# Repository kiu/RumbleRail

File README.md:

RumbleRail
==========

a standalone and modular floppy music player

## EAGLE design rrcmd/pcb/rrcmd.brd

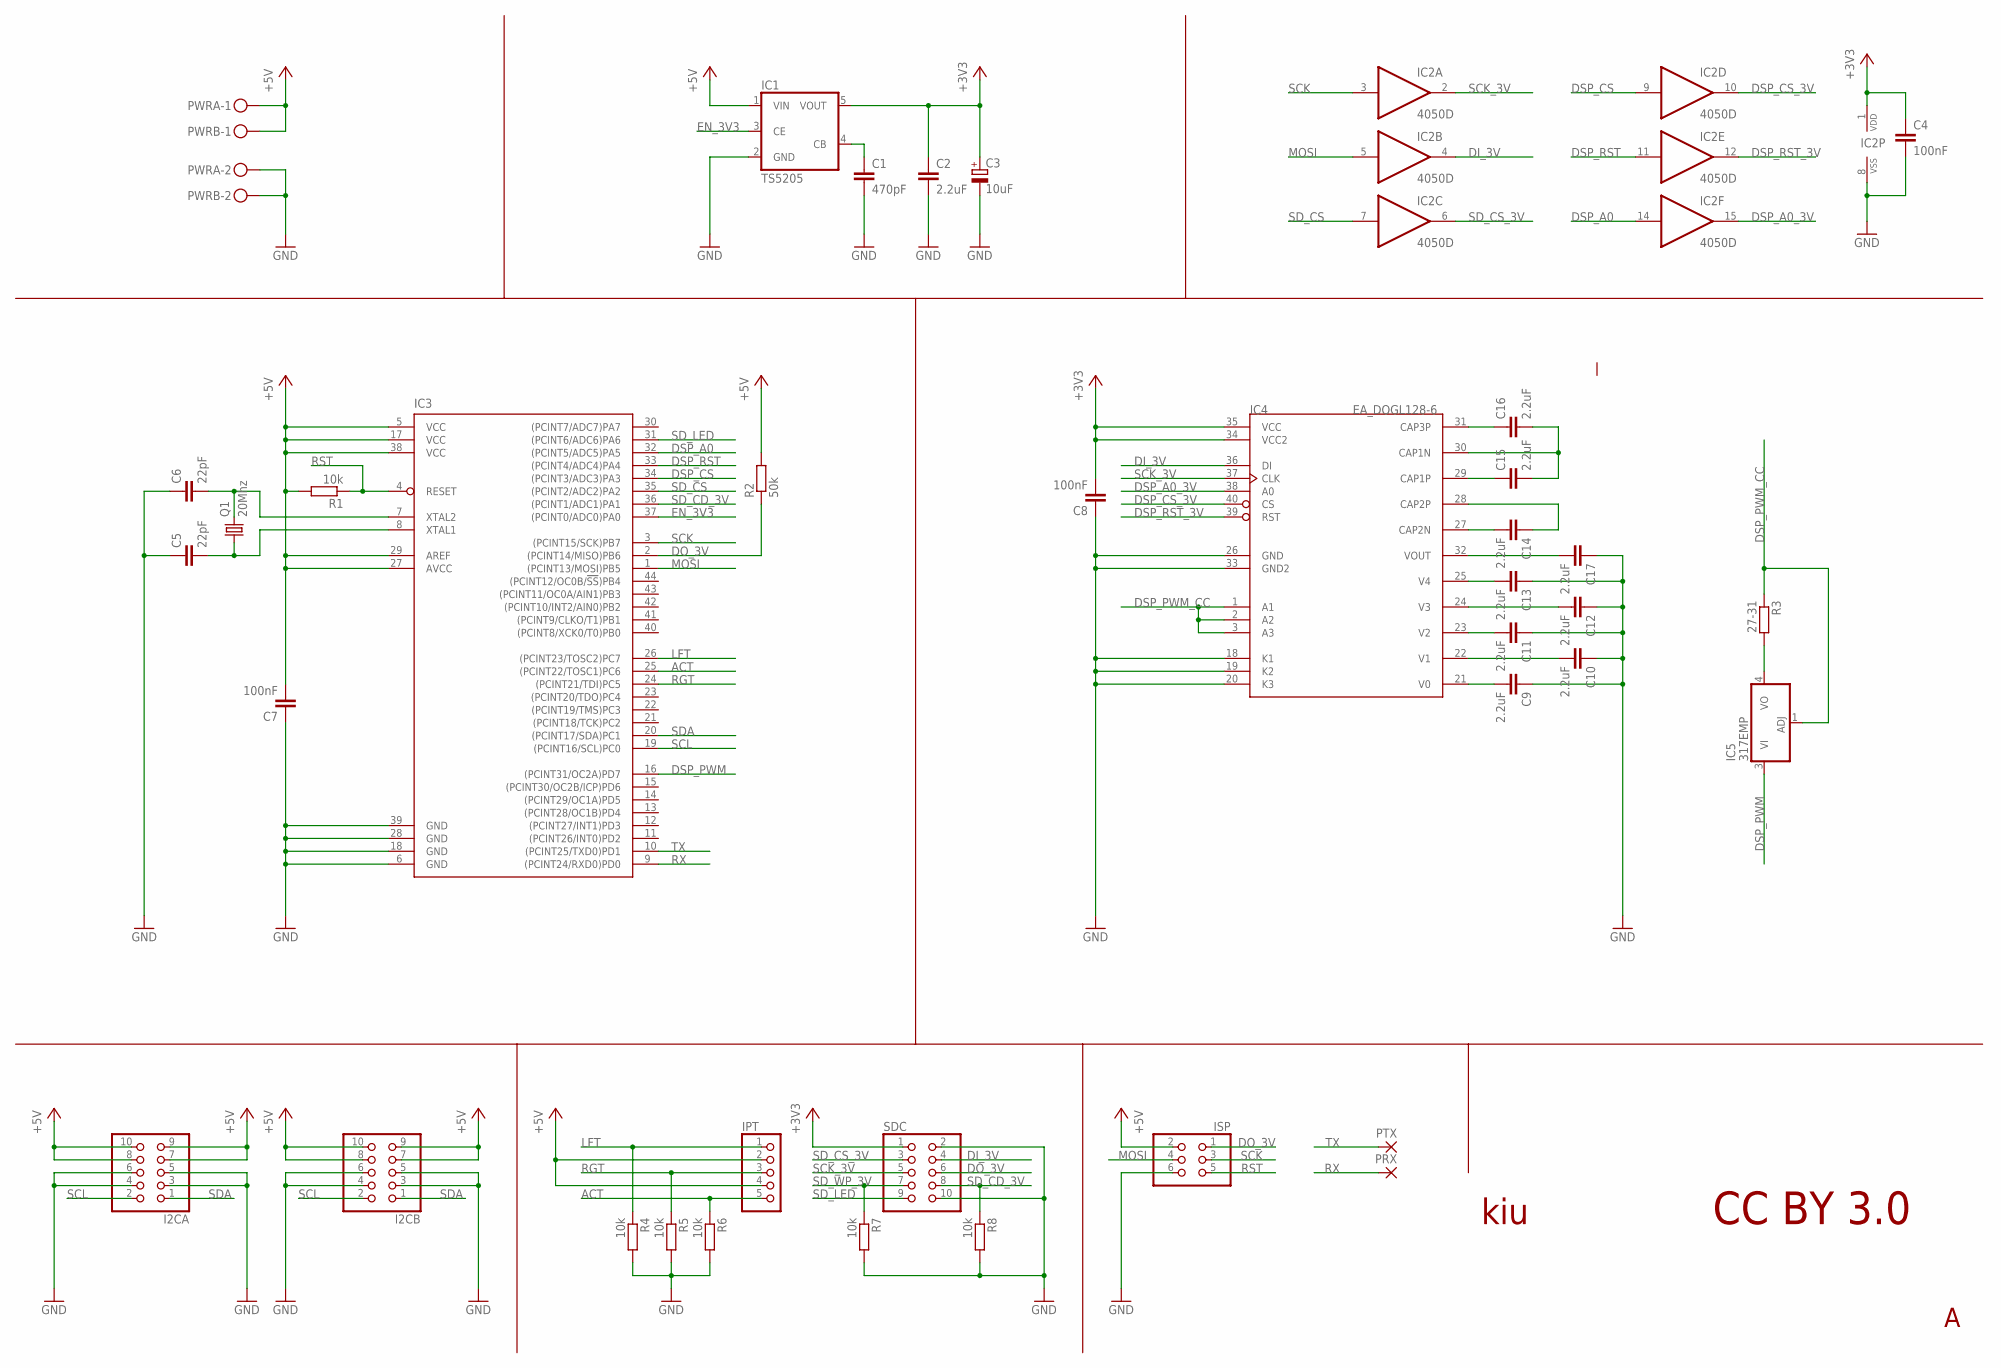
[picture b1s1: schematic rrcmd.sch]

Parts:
C1: 470pF; C0805
C2, C9, C10, C11, C12, C13, C14, C15, C16, C17: 2.2uF; C0805
C3: 10uF; CT3216
C4, C7, C8: 100nF; C0805
C5, C6: 22pF; C0805
I2CA, I2CB: PINHD-2X5; 2X05
IC1: TS5205; SOT25
IC2: 4050D; SO16
IC3: ATMEGA644A; TQFP44
IC4: EA_DOGL128-6
IC5: 317EMP; SOT223
IPT: PINHD-1X5; 1X05
ISP: PINHD-2X3; 2X03
PRX: SMD2; SMD1,27-2,54
PTX: SMD2; SMD1,27-2,54
PWRA: MKDSN1,5/2-5,08
PWRB: MKDSN1,5/2-5,08
Q1: 20Mhz; HC49UP
R1, R4, R5, R6, R7, R8: 10k; R0805
R2: 50k; R0805
R3: 27-31; R0805
SDC: PINHD-2X5; 2X05

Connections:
+3V3: C2.1, C3.+, C4.1, C8.2, IC1.5 (VOUT), IC2.1 (VDD), IC4.34 (VCC2), IC4.35 (VCC), SDC.1
+5V: C7.2, I2CA.7, I2CA.8, I2CA.9, I2CA.10, I2CB.7, I2CB.8, I2CB.9, I2CB.10, IC1.1 (VIN), IC3.5 (VCC), IC3.17 (VCC), IC3.27 (AVCC), IC3.29 (AREF), IC3.38 (VCC), IPT.2, IPT.4, ISP.2, PWRA.1, PWRB.1, R1.2, R2.2
ACT: IC3.25 ((PCINT22/TOSC1)PC6), IPT.5, R6.1
CAP1N: C15.2, C16.2, IC4.30 (CAP1N)
CAP1P: C15.1, IC4.29 (CAP1P)
CAP2N: C14.2, IC4.27 (CAP2N)
CAP2P: C14.1, IC4.28 (CAP2P)
CAP3P: C16.1, IC4.31 (CAP3P)
DI_3V: IC2.4 (O), IC4.36 (DI), SDC.4
DO_3V: IC3.2 ((PCINT14/MISO)PB6), ISP.1, R2.1, SDC.6
DSP_A0: IC2.14 (I), IC3.32 ((PCINT5/ADC5)PA5)
DSP_A0_3V: IC2.15 (O), IC4.38 (A0)
DSP_CS: IC2.9 (I), IC3.34 ((PCINT3/ADC3)PA3)
DSP_CS_3V: IC2.10 (O), IC4.40 (CS)
DSP_PWM: IC3.16 ((PCINT31/OC2A)PD7), IC5.3 (VI)
DSP_PWM_CC: IC4.1 (A1), IC4.2 (A2), IC4.3 (A3), IC5.1 (ADJ), R3.1
DSP_RST: IC2.11 (I), IC3.33 ((PCINT4/ADC4)PA4)
DSP_RST_3V: IC2.12 (O), IC4.39 (RST)
EN_3V3: IC1.3 (CE), IC3.37 ((PCINT0/ADC0)PA0)
GND: C1.2, C2.2, C3.-, C4.2, C5.1, C6.1, C7.1, C8.1, C9.1, C10.1, C11.1, C12.1, C13.1, C17.1, I2CA.3, I2CA.4, I2CA.5, I2CA.6, I2CB.3, I2CB.4, I2CB.5, I2CB.6, IC1.2 (GND), IC2.8 (VSS), IC3.6 (GND), IC3.18 (GND), IC3.28 (GND), IC3.39 (GND), IC4.18 (K1), IC4.19 (K2), IC4.20 (K3), IC4.26 (GND), IC4.33 (GND2), ISP.6, PWRA.2, PWRB.2, R4.2, R5.2, R6.2, R7.2, R8.2, SDC.2, SDC.10
LFT: IC3.26 ((PCINT23/TOSC2)PC7), IPT.1, R4.1
MOSI: IC2.5 (I), IC3.1 ((PCINT13/MOSI)PB5), ISP.4
unnamed: C1.1, IC1.4 (CB)
unnamed: C12.2, IC4.24 (V3)
unnamed: C13.2, IC4.25 (V4)
unnamed: C11.2, IC4.23 (V2)
unnamed: C10.2, IC4.22 (V1)
unnamed: C9.2, IC4.21 (V0)
unnamed: C17.2, IC4.32 (VOUT)
unnamed: IC5.4 (VO), R3.2
unnamed: C6.2, IC3.7 (XTAL2), Q1.2
unnamed: C5.2, IC3.8 (XTAL1), Q1.1
RGT: IC3.24 ((PCINT21/TDI)PC5), IPT.3, R5.1
RST: IC3.4 (RESET), ISP.5, R1.1
RX: IC3.9 ((PCINT24/RXD0)PD0), PRX.1
SCK: IC2.3 (I), IC3.3 ((PCINT15/SCK)PB7), ISP.3
SCK_3V: IC2.2 (O), IC4.37 (CLK), SDC.5
SCL: I2CA.2, I2CB.2, IC3.19 ((PCINT16/SCL)PC0)
SDA: I2CA.1, I2CB.1, IC3.20 ((PCINT17/SDA)PC1)
SD_CD_3V: IC3.36 ((PCINT1/ADC1)PA1), R8.1, SDC.8
SD_CS: IC2.7 (I), IC3.35 ((PCINT2/ADC2)PA2)
SD_CS_3V: IC2.6 (O), SDC.3
SD_LED: IC3.31 ((PCINT6/ADC6)PA6), SDC.9
SD_WP_3V: R7.1, SDC.7
TX: IC3.10 ((PCINT25/TXD0)PD1), PTX.1

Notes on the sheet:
CC BY 3.0
kiu

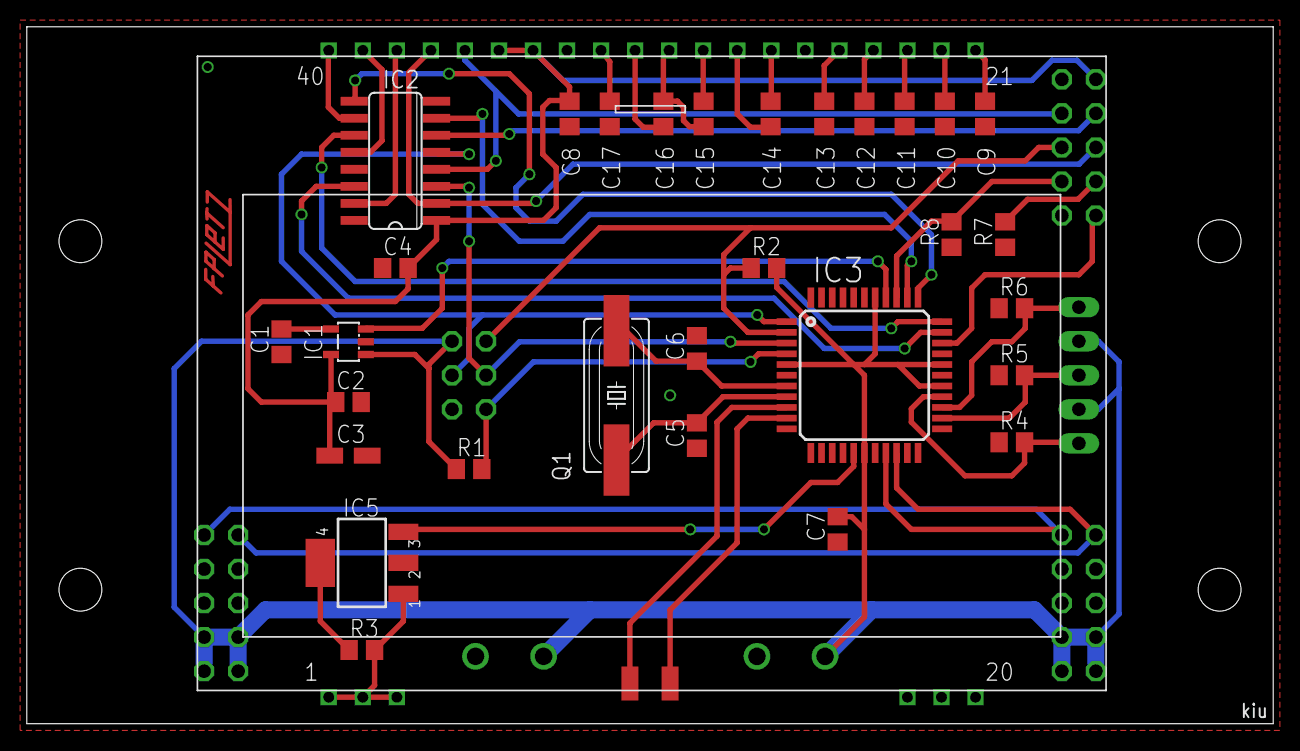
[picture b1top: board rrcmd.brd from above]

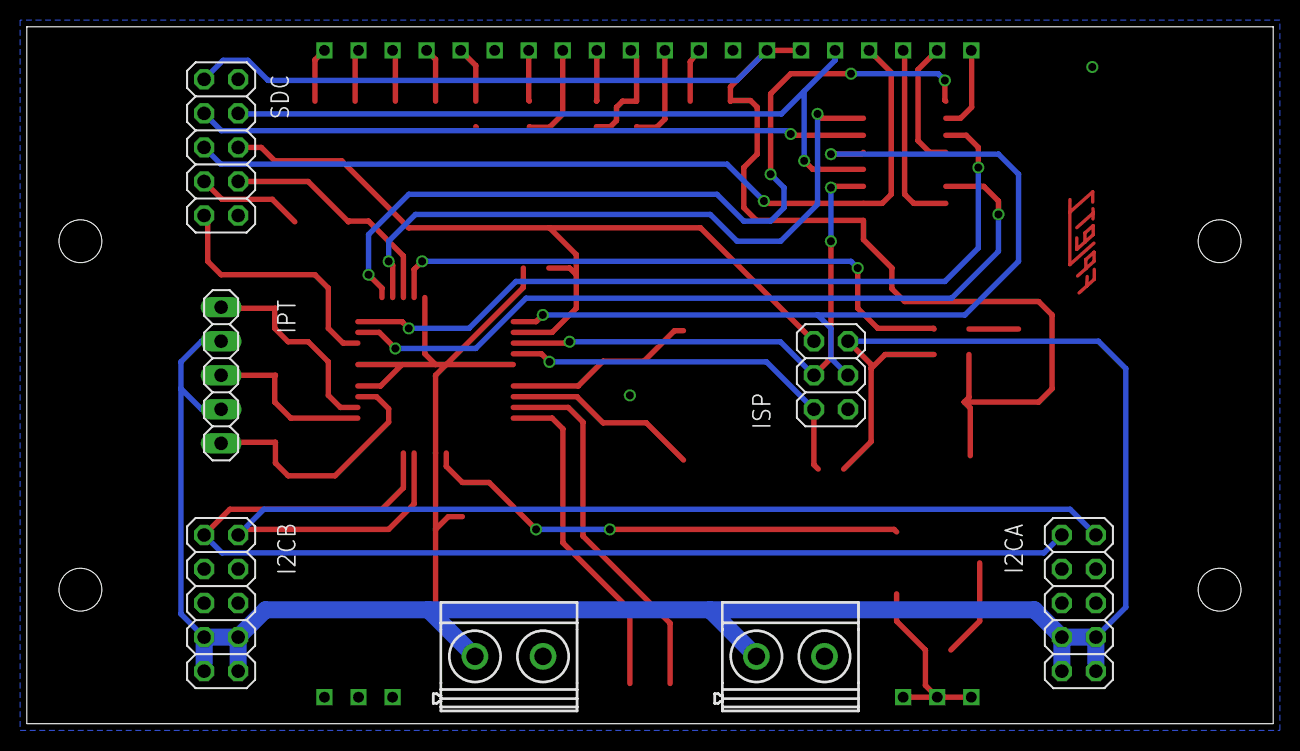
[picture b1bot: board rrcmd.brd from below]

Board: 4 copper layers, 93.0 x 52.0 mm, 40 parts (7 on the bottom side), 45 nets.

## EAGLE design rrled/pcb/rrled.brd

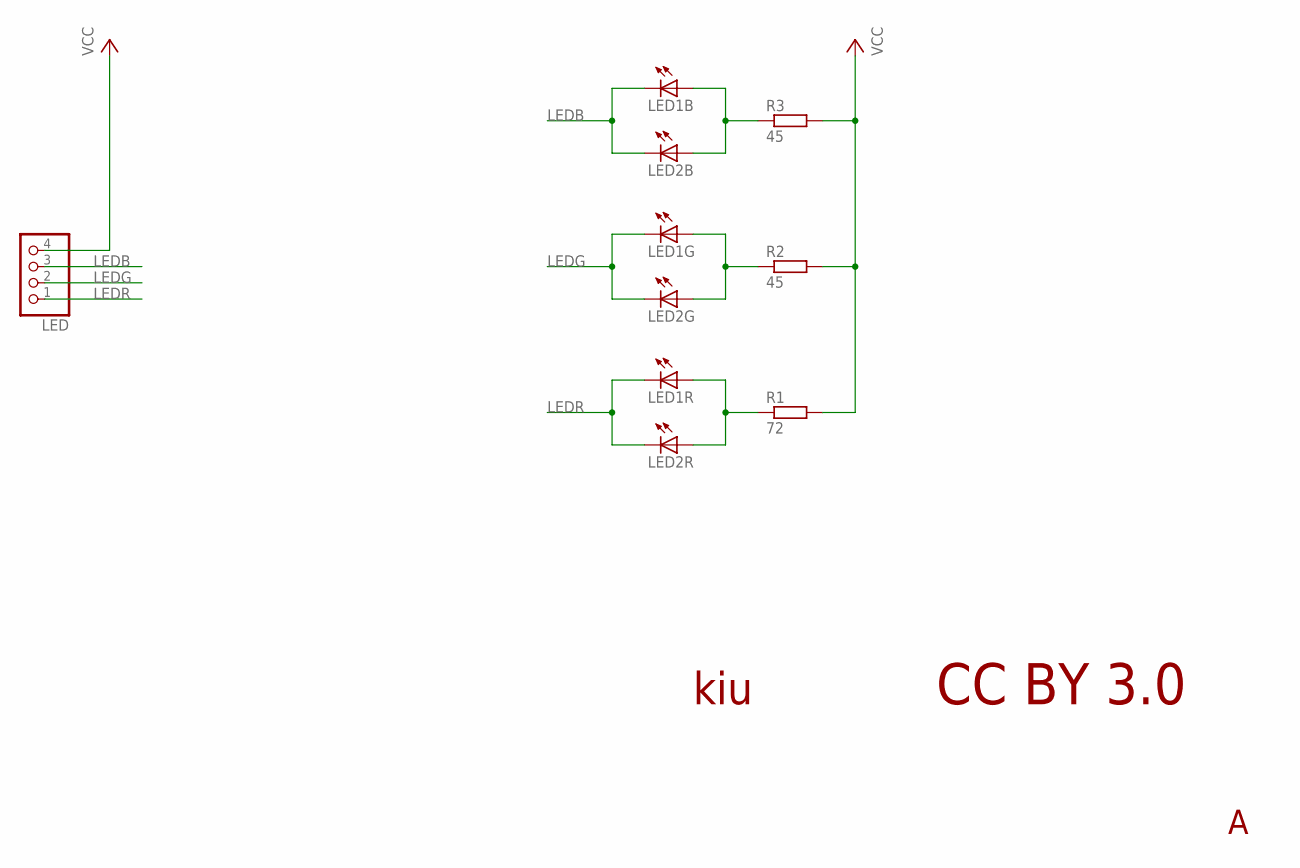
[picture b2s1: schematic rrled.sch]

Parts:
LED: PINHD-1X4; 1X04
LED1, LED2: MULTILED_LRTB_G6TG; P-LCC-6_TOPLED
R1: 72; R0603
R2, R3: 45; R0603

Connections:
LEDB: LED.3, LED1.C3 (C), LED2.C3 (C)
LEDG: LED.2, LED1.C2 (C), LED2.C2 (C)
LEDR: LED.1, LED1.C1 (C), LED2.C1 (C)
unnamed: LED1.A2 (A), LED2.A2 (A), R2.1
unnamed: LED1.A3 (A), LED2.A3 (A), R3.1
unnamed: LED1.A1 (A), LED2.A1 (A), R1.1
VCC: LED.4, R1.2, R2.2, R3.2

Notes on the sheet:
CC BY 3.0
kiu

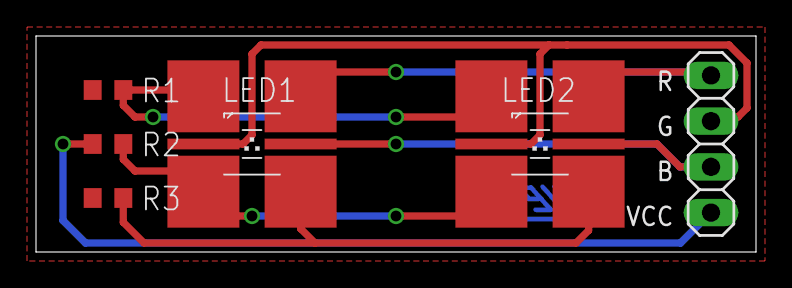
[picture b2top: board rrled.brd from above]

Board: 4 copper layers, 40.0 x 12.0 mm, 6 parts (0 on the bottom side), 7 nets.

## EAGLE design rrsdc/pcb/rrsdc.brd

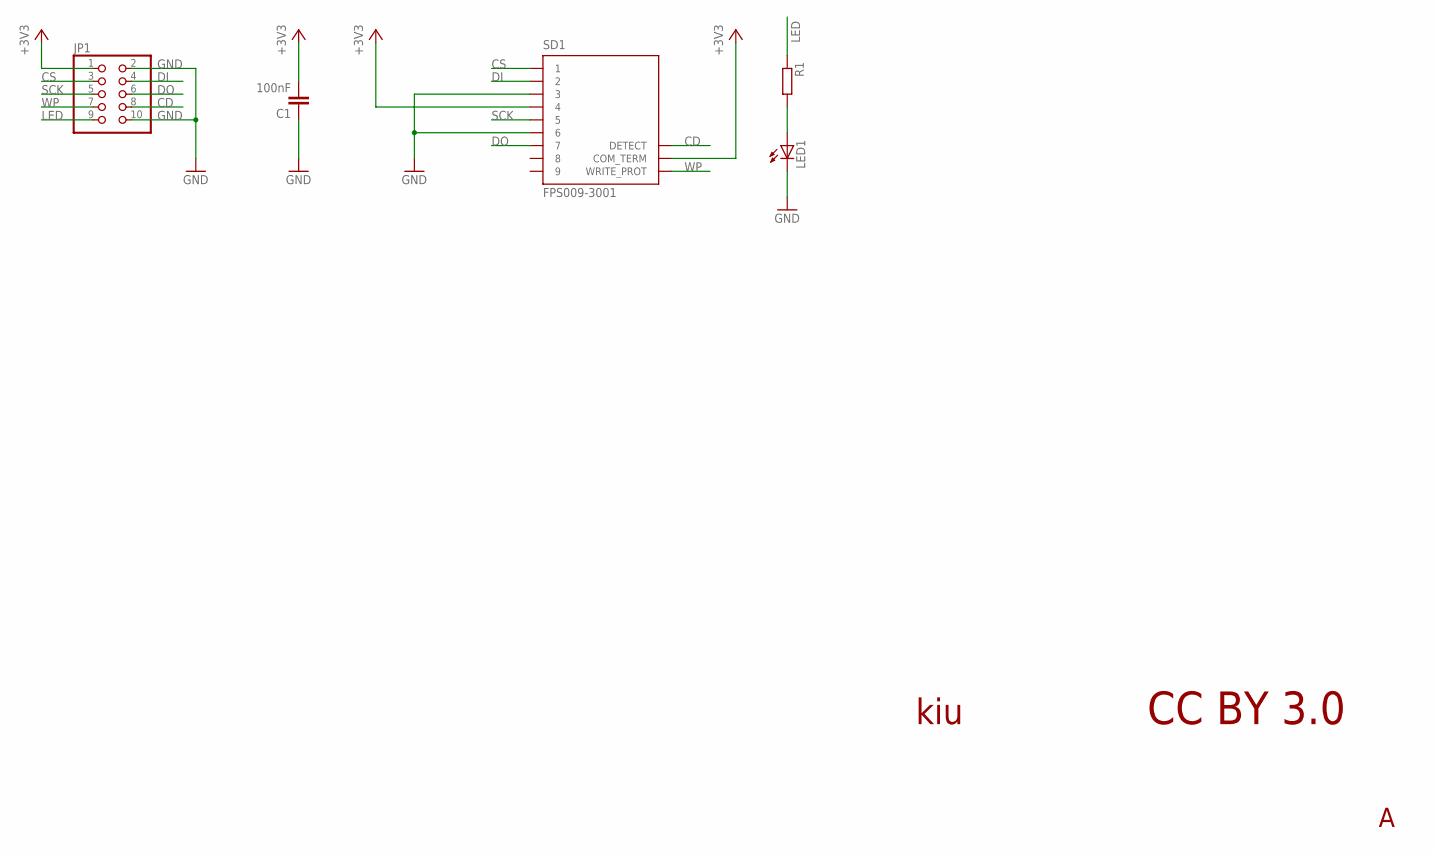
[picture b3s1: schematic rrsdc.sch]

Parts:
C1: 100nF; C0805
JP1: PINHD-2X5; 2X05
LED1: SIDELEDPLCC-NOTHERM; PLCC-2-NOTHERM
R1: R-EU_R0805; R0805
SD1: FPS009-3001; FPS009-3000

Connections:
+3V3: C1.2, JP1.1, SD1.4, SD1.COM_TERM
CD: JP1.8, SD1.DETECT
CS: JP1.3, SD1.1
DI: JP1.4, SD1.2
DO: JP1.6, SD1.7
GND: C1.1, JP1.2, JP1.10, LED1.C, SD1.3, SD1.6
LED: JP1.9, R1.1
unnamed: LED1.A, R1.2
SCK: JP1.5, SD1.5
WP: JP1.7, SD1.WRITE_PROT

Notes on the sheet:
CC BY 3.0
kiu

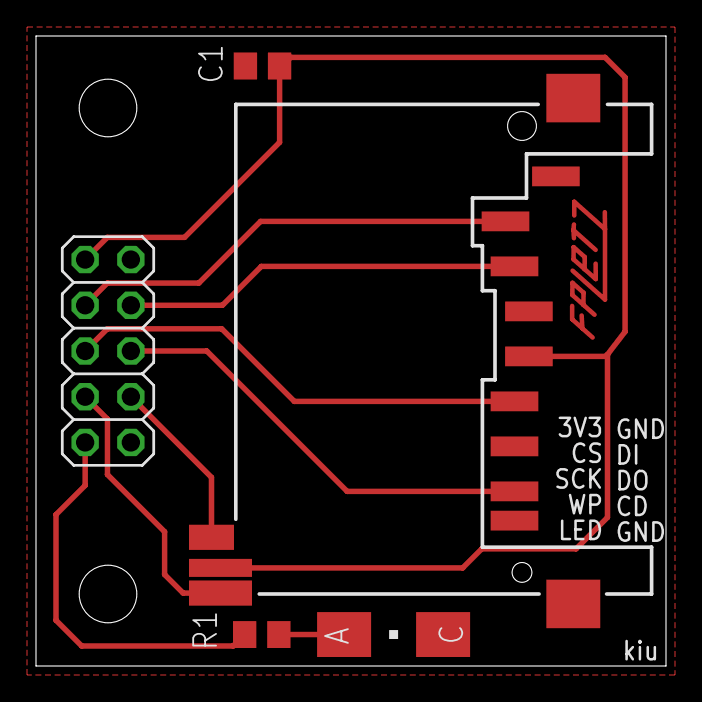
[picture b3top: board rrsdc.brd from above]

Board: 4 copper layers, 35.0 x 35.0 mm, 5 parts (0 on the bottom side), 10 nets.

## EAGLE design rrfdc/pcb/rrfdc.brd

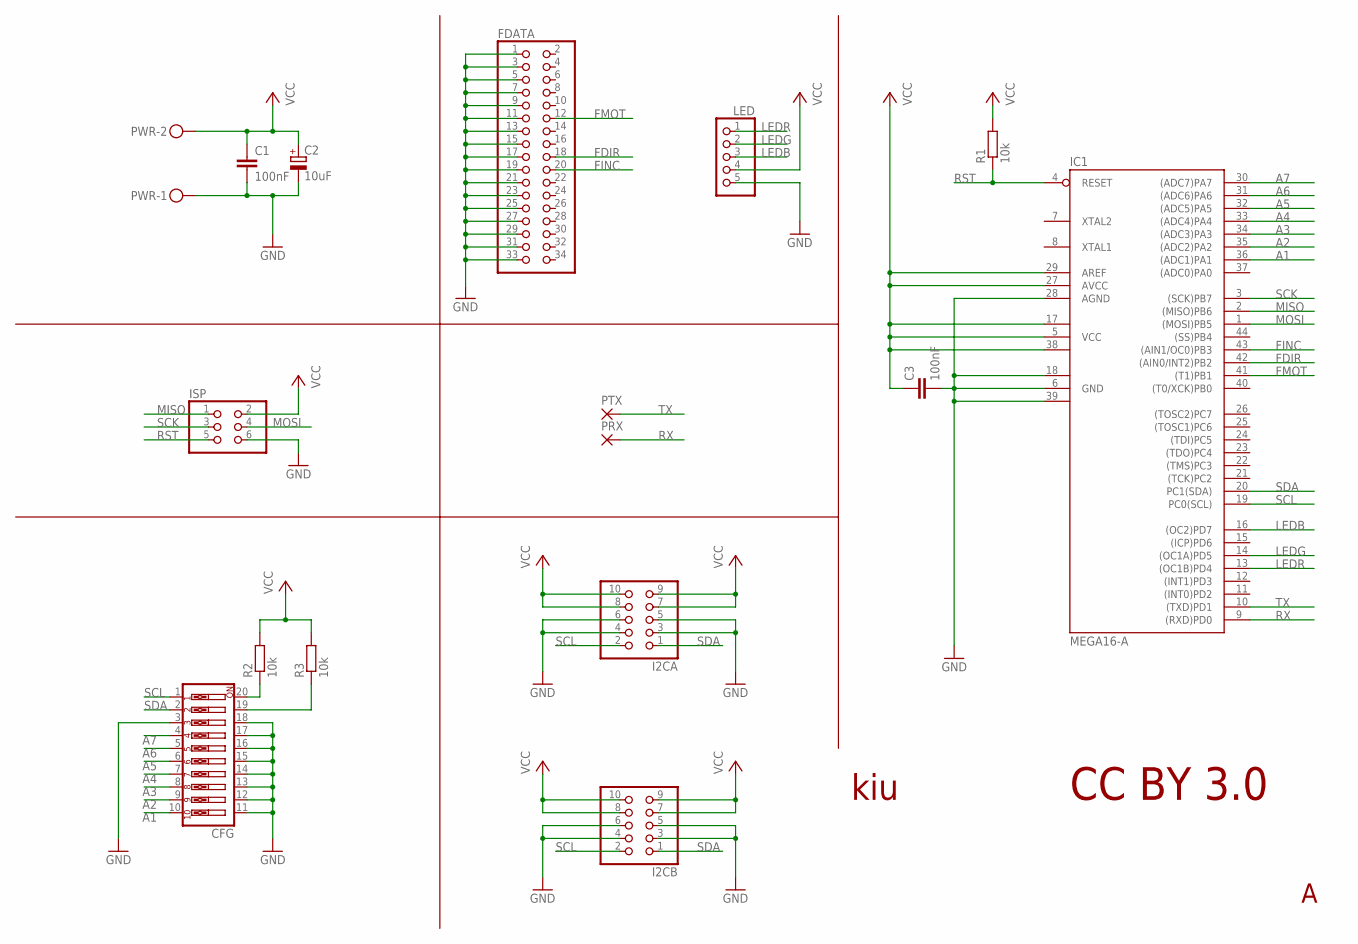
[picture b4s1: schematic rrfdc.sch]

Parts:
C1, C3: 100nF; C0805
C2: 10uF; CT3216
CFG: SW_DIP-10; EDG-10
FDATA: PINHD-2X17; 2X17
I2CA, I2CB: PINHD-2X5; 2X05
IC1: MEGA16-A; TQFP44
ISP: PINHD-2X3; 2X03
LED: PINHD-1X5; 1X05
PRX: SMD2; SMD1,27-2,54
PTX: SMD2; SMD1,27-2,54
PWR: MKDSN1,5/2-5,08
R1, R2, R3: 10k; R0805

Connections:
A1: CFG.10, IC1.36 ((ADC1)PA1)
A2: CFG.9, IC1.35 ((ADC2)PA2)
A3: CFG.8, IC1.34 ((ADC3)PA3)
A4: CFG.7, IC1.33 ((ADC4)PA4)
A5: CFG.6, IC1.32 ((ADC5)PA5)
A6: CFG.5, IC1.31 ((ADC6)PA6)
A7: CFG.4, IC1.30 ((ADC7)PA7)
FDIR: FDATA.18, IC1.42 ((AIN0/INT2)PB2)
FINC: FDATA.20, IC1.43 ((AIN1/OC0)PB3)
FMOT: FDATA.12, IC1.41 ((T1)PB1)
GND: C1.2, C2.-, C3.2, CFG.3, CFG.11, CFG.12, CFG.13, CFG.14, CFG.15, CFG.16, CFG.17, CFG.18, FDATA.1, FDATA.3, FDATA.5, FDATA.7, FDATA.9, FDATA.11, FDATA.13, FDATA.15, FDATA.17, FDATA.19, FDATA.21, FDATA.23, FDATA.25, FDATA.27, FDATA.29, FDATA.31, FDATA.33, I2CA.3, I2CA.4, I2CA.5, I2CA.6, I2CB.3, I2CB.4, I2CB.5, I2CB.6, IC1.6 (GND), IC1.18 (GND1), IC1.28 (AGND), IC1.39 (GND2), ISP.6, LED.5, PWR.1
LEDB: IC1.16 ((OC2)PD7), LED.3
LEDG: IC1.14 ((OC1A)PD5), LED.2
LEDR: IC1.13 ((OC1B)PD4), LED.1
MISO: IC1.2 ((MISO)PB6), ISP.1
MOSI: IC1.1 ((MOSI)PB5), ISP.4
unnamed: CFG.20, R2.1
unnamed: CFG.19, R3.1
RST: IC1.4 (RESET), ISP.5, R1.1
RX: IC1.9 ((RXD)PD0), PRX.1
SCK: IC1.3 ((SCK)PB7), ISP.3
SCL: CFG.1, I2CA.2, I2CB.2, IC1.19 (PC0(SCL))
SDA: CFG.2, I2CA.1, I2CB.1, IC1.20 (PC1(SDA))
TX: IC1.10 ((TXD)PD1), PTX.1
VCC: C1.1, C2.+, C3.1, I2CA.7, I2CA.8, I2CA.9, I2CA.10, I2CB.7, I2CB.8, I2CB.9, I2CB.10, IC1.5 (VCC), IC1.17 (VCC1), IC1.27 (AVCC), IC1.29 (AREF), IC1.38 (VCC2), ISP.2, LED.4, PWR.2, R1.2, R2.2, R3.2

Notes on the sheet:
CC BY 3.0
kiu

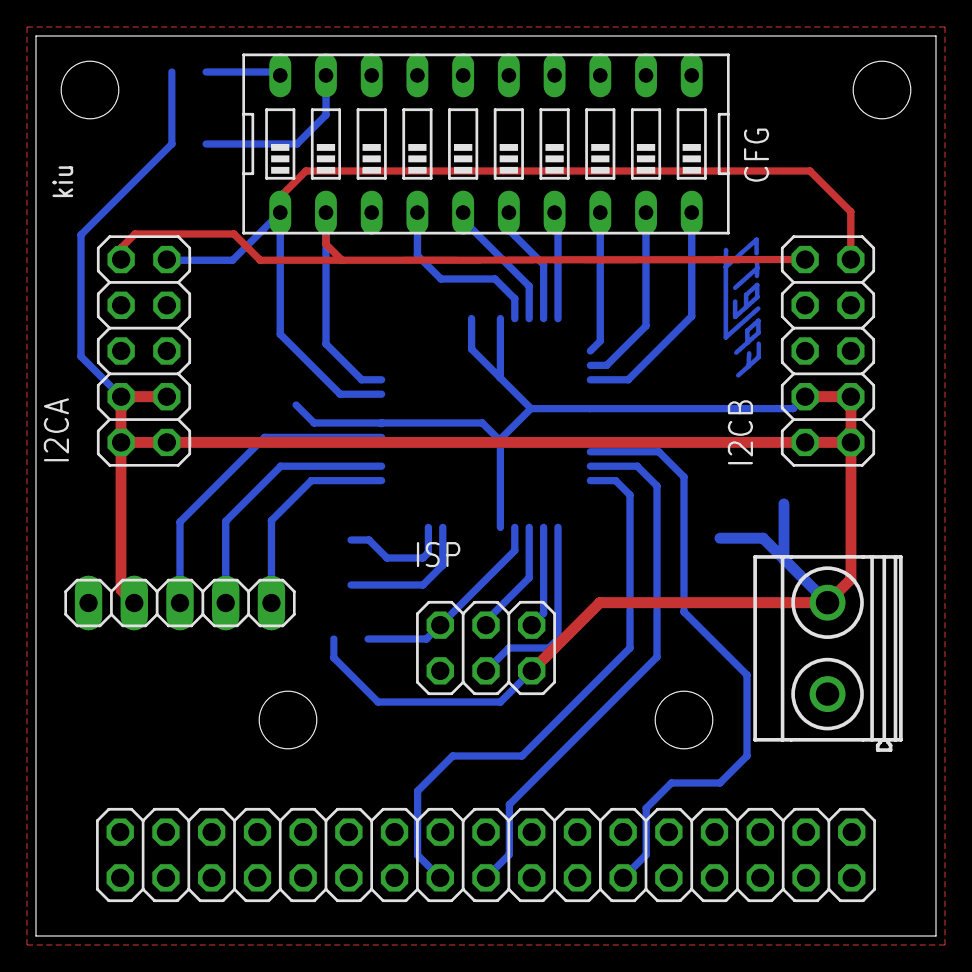
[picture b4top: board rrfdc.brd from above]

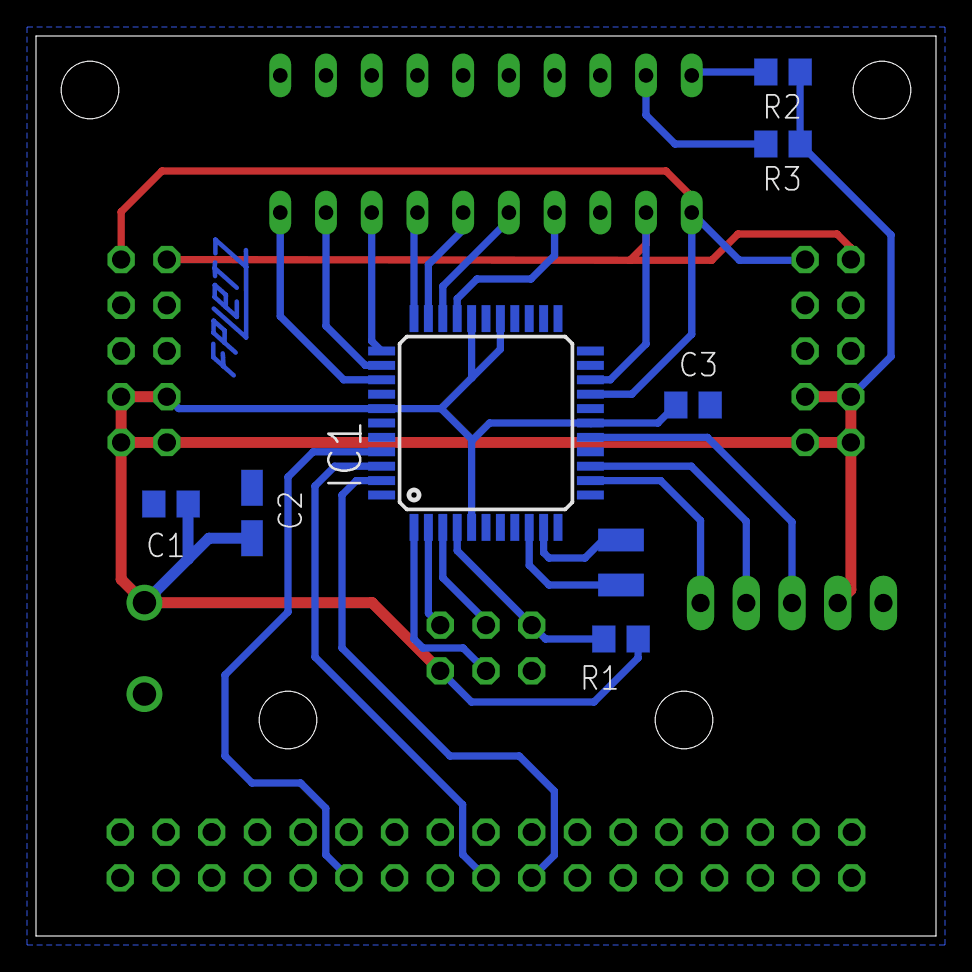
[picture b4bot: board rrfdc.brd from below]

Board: 4 copper layers, 50.0 x 50.0 mm, 16 parts (9 on the bottom side), 25 nets.

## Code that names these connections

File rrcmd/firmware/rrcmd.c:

#include "rrcmd.h"


#include "midi.h"
#include "dir.h"
#include "screen.h"
//#include "screen_dummy.h"
#include <avr/interrupt.h>
#include <util/delay.h>
#include "lib/i2c/i2cmaster.h"
#include "lib/uart/uart.h"

uint8_t floppy_count = 0;
uint8_t floppy_addr[MAX_FLOPPIES];

volatile uint8_t btn_state = 0;
volatile uint8_t e_btn = 0;
volatile uint8_t e_sd = 0;

unsigned char i2c_ret;
uint8_t ferr;

// ---------------------------------------

uint8_t get_floppy_count() {
	return floppy_count;
}

// ---------------------------------------

uint8_t sendI2C_addr(uint8_t addr, uint8_t cmd) {
#ifdef DEBUG
	sprintf(out, "S: %02x %02x\r\n", addr, cmd);
	uart_puts(out);
#endif

	i2c_ret = i2c_start(addr + I2C_WRITE);

	if (i2c_ret == 0) {
		i2c_ret = i2c_write(cmd);
	}

	i2c_stop();
	return i2c_ret;
}

uint8_t sendI2C_id(uint8_t id, uint8_t cmd) {
	if (id >= floppy_count) {
		return 1;
	}
	return sendI2C_addr(floppy_addr[id], cmd);
}

void scanI2C(void) {
	uart_puts("I2C device discovery:");

	for (uint8_t addr = 2; addr != 0xFE; addr += 2) {
		if (sendI2C_addr(addr, 0x80) == 0) {
			floppy_addr[floppy_count] = addr;
			floppy_count++;
			sprintf(out, " %02x", addr);
			uart_puts(out);
		}
	}
	uart_puts("\r\n");
}

// ---------------------------------------

void song_stop(void) {
	TIMSK1 &= ~(1 << OCIE1A);
	for (uint8_t i = 0; i < floppy_count; i++) {
		sendI2C_id(i, 0xFD);	
	}
}

void song_start(void) {
	for (uint8_t i = 0; i < floppy_count; i++) {
		sendI2C_id(i, 0xFE);	
	}

	FILINFO fiplay = dir_get_file();
	ferr = midi_init(fiplay);
	if (ferr != FR_OK) {
		song_stop();
		return;
	}
	
	screen_draw(SCR_PLAY);

	TIMSK1 |= (1 << OCIE1A);
}

// ---------------------------------------

ISR(TIMER1_COMPA_vect) {
	if (midi_tick()) {
		song_stop();
	}
}

ISR (PCINT0_vect) {
	if (PINA & (1 << PA1)) {
		e_sd = 1; // SD inserted
	} else {
		e_sd = 2; // SD removed
	}
}

ISR (PCINT2_vect) {
	uint8_t pin = PINC;
	uint8_t lft = pin & (1<<PC7);
	uint8_t act = pin & (1<<PC6);
	uint8_t rgt = pin & (1<<PC5);

	if (!lft && !rgt) {
		btn_state = 0;
	}
	if (btn_state) {
		return;
	}

	if (act) {
		e_btn = 1;
	}

	if (lft && !rgt) {
		btn_state = 1;
		e_btn = 2;
	}


	if (rgt && !lft) {
		btn_state = 1;
		e_btn = 3;
	}

}

// ---------------------------------------

int main (void) {
	// Prepare PWR
	sbi(DDRA, PA0); // EN_3V3
	sbi(PORTA, PA0);

	// Prepare SPI
	sbi(DDRB, PB7);  // SCK
	cbi(PORTB, PB6); // DI
	cbi(DDRB, PB6);  // DI
	sbi(DDRB, PB5);  // DO
	sbi(DDRB, PB4);  // SS

	//SPCR = (1<<MSTR) | (1<<SPR1) | (1<<SPR0) | (1<<SPE); // clk/64
	//SPSR |= (1<<SPI2X);

	// Prepare display
	sbi(DDRA, PA5);  // A0
	sbi(DDRA, PA4);  // Reset
	sbi(DDRA, PA3);  // CS
	sbi(DDRD, PD7);  // Backlight

	// Prepare MMC
	sbi(DDRA, PA2); // CS
	cbi(PORTA, PA1); // CD
	cbi(DDRA, PA1); // CD
	PCMSK0 |= (1 << PCINT1);
	PCICR |= (1 << PCIE0);

	// Prepare buttons
	cbi(PORTC, PC5); // Previous
	cbi(DDRC, PC5);	
	PCMSK2 |= (1 << PCINT21);

	cbi(PORTC, PC6); // Action
	cbi(DDRC, PC6);
	PCMSK2 |= (1 << PCINT22);

	cbi(PORTC, PC7); // Next
	cbi(DDRC, PC7);
	PCMSK2 |= (1 << PCINT23);

	PCICR |= (1 << PCIE2);

	sei();

	// Init backlight: Fast PWM, clear, clk/8
	OCR2A = LCD_PWM;
	TCCR2A = (1 << COM2A1) | (1 << WGM21) | (1 << WGM20);
	TCCR2B = (1 << CS21);
	sbi(PORTD, PD7); // Backlight

	OCR1A = 0x00A2;
	TCCR1B |= (1 << WGM12); // CTC
	TCCR1B |= (1 << CS12) | (1 << CS10); // Prescaler 1024

	uart_init(UART_BAUD_SELECT_DOUBLE_SPEED(UART_BAUD_RATE, F_CPU)); 
	uart_puts("\r\nfdsp http://schoar.de/tinkering/xxx\r\n");

	screen_init();
	_delay_ms(2000);

	screen_draw(SCR_BOOT);
	_delay_ms(2000);

	screen_draw(SCR_DISCOVER);
	_delay_ms(2000);

	i2c_init();
	scanI2C();

	screen_draw(SCR_DISCOVER_RESULT);
	_delay_ms(2000);

	e_sd = 1;

	while (1) {

		if (e_sd != 0) {
			if (e_sd == 1) {
				if (dir_init() == 0 && dir_mount() == 0) {
					screen_draw(SCR_SELECT);
					uart_puts("SD Card inserted\r\n");
				} else {
					e_sd = 2;
				}
			}
			if (e_sd == 2) {
				song_stop();
				dir_umount();
				screen_draw(SCR_INSERT);
				uart_puts("Insert SD Card\r\n");
			}
			_delay_ms(20);
			e_sd = 0;
		}

		if (e_btn != 0) {
			if (e_btn == 1) {
				song_stop();				

				song_start();
			}
			if (e_btn == 2) {
				song_stop();
				dir_prev();
				screen_draw(SCR_SELECT);
			} 
			if (e_btn == 3) {
				song_stop();
				dir_next();
				screen_draw(SCR_SELECT);
			}
			e_btn = 0;
		}

	}

	uart_puts("Shutdown...\r\n");

	for (uint8_t i = 0; i < floppy_count; i++) {
		sendI2C_id(i, 0xFF);	
	}

	cbi(PORTD, PD7); // Backlight Off
	cbi(PORTA, PA0); // 3v3 off

	cli();

	return 0;
}

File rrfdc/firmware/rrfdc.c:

#include "rrfdc.h"

#include <avr/io.h>
#include <avr/interrupt.h>
#include <avr/sleep.h>

#include <util/delay.h>
#include <util/twi.h>

#include "lib/uart/uart.h"
#include "global.h"

const uint8_t FLOPPY_MAX_NOTE = 59;
const uint8_t FLOPPY_MAX_POS = 158;

enum MODE {INIT, IDLE, RUN, OFF};
volatile enum MODE mode = INIT;

volatile uint8_t floppy_pos;

volatile uint8_t led_i = 0;
volatile uint8_t led_r = 0;
volatile uint8_t led_g = 0;
volatile uint8_t led_b = 0;

char out[80];

static const uint16_t note_tick[] = {
/*
import math
tick = float(8000000) / 8
for note in range(0,128):
	freq = pow(2,(float(note)-69)/12) * 440 * 2
	ocr = int(tick / freq)
	print "\t%d, // Note %d" % (ocr, note)
*/
	61156, // Note 0
	57723, // Note 1
	54483, // Note 2
	51425, // Note 3
	48539, // Note 4
	45815, // Note 5
	43243, // Note 6
	40816, // Note 7
	38525, // Note 8
	36363, // Note 9
	34322, // Note 10
	32396, // Note 11
	30578, // Note 12
	28861, // Note 13
	27241, // Note 14
	25712, // Note 15
	24269, // Note 16
	22907, // Note 17
	21621, // Note 18
	20408, // Note 19
	19262, // Note 20
	18181, // Note 21
	17161, // Note 22
	16198, // Note 23
	15289, // Note 24
	14430, // Note 25
	13620, // Note 26
	12856, // Note 27
	12134, // Note 28
	11453, // Note 29
	10810, // Note 30
	10204, // Note 31
	9631, // Note 32
	9090, // Note 33
	8580, // Note 34
	8099, // Note 35
	7644, // Note 36
	7215, // Note 37
	6810, // Note 38
	6428, // Note 39
	6067, // Note 40
	5726, // Note 41
	5405, // Note 42
	5102, // Note 43
	4815, // Note 44
	4545, // Note 45
	4290, // Note 46
	4049, // Note 47
	3822, // Note 48
	3607, // Note 49
	3405, // Note 50
	3214, // Note 51
	3033, // Note 52
	2863, // Note 53
	2702, // Note 54
	2551, // Note 55
	2407, // Note 56
	2272, // Note 57
	2145, // Note 58
	2024, // Note 59
	1911, // Note 60
	1803, // Note 61
	1702, // Note 62
	1607, // Note 63
	1516, // Note 64
	1431, // Note 65
	1351, // Note 66
	1275, // Note 67
	1203, // Note 68
	1136, // Note 69
	1072, // Note 70
	1012, // Note 71
	955, // Note 72
	901, // Note 73
	851, // Note 74
	803, // Note 75
	758, // Note 76
	715, // Note 77
	675, // Note 78
	637, // Note 79
	601, // Note 80
	568, // Note 81
	536, // Note 82
	506, // Note 83
	477, // Note 84
	450, // Note 85
	425, // Note 86
	401, // Note 87
	379, // Note 88
	357, // Note 89
	337, // Note 90
	318, // Note 91
	300, // Note 92
	284, // Note 93
	268, // Note 94
	253, // Note 95
	238, // Note 96
	225, // Note 97
	212, // Note 98
	200, // Note 99
	189, // Note 100
	178, // Note 101
	168, // Note 102
	159, // Note 103
	150, // Note 104
	142, // Note 105
	134, // Note 106
	126, // Note 107
	119, // Note 108
	112, // Note 109
	106, // Note 110
	100, // Note 111
	94, // Note 112
	89, // Note 113
	84, // Note 114
	79, // Note 115
	75, // Note 116
	71, // Note 117
	67, // Note 118
	63, // Note 119
	59, // Note 120
	56, // Note 121
	53, // Note 122
	50, // Note 123
	47, // Note 124
	44, // Note 125
	42, // Note 126
	39, // Note 127

};

static const uint32_t  note_led[] = {
	// red
	0x00FF0000, // C
	0x00FF2222, // C#

	// orange
	0x00FFFF00, // D
	0x00FF6600, // D#

	// purple
	0x00FF00FF, // E

	// blue
	0x000000FF, // F
	0x002222FF, // F#

	// turqoise
	0x0000FFFF, // G
	0x0033DDDD, // G#

	// green
	0x0000FF00, // A
	0x0022FF22, // A#

	// white
	0x00FFFFFF // H
};

void set_led32(uint32_t color) {
	led_r = color >> 16;
	led_g = color >> 8;
	led_b = color >> 0;
}

void cmd(uint8_t cmd) {
	if (cmd == 0xFF) { 
		mode = OFF;
		return;
	}

	if (cmd == 0xFE) { 
		TIMSK |= (1 << OCIE2); // LED Timer On
		cbi(PORTB, PB1); // Enable motor
		mode = RUN;
		return;
	}

	if (cmd == 0xFD) { 
		mode = IDLE;
		set_led32(0x00000000);
		TIMSK &= ~(1 << OCIE1A); // Floppy Timer Off
		TIMSK &= ~(1 << OCIE2); // LED Timer Off
		sbi(PORTD, PD4); sbi(PORTD, PD5); sbi(PORTD, PD7); // LEDs off
		sbi(PORTB, PB1); // Disable motor
		return;
	}

	if (mode != RUN) {
		return;
	}

	// Note off
	if (cmd == 0x80) { 
		TIMSK &= ~(1 << OCIE1A);
		set_led32(0x00000000);
		return;
	}

	// Note on
	if (cmd <= FLOPPY_MAX_NOTE) {
		OCR1A = note_tick[cmd];
		TCNT1 = 0;
		TIMSK |= (1 << OCIE1A);
		set_led32(note_led[cmd % 12]);
		return;
	}
}

ISR(TWI_vect){
	// own address has been acknowledged
	if( (TWSR & 0xF8) == TW_SR_SLA_ACK ){  
		// prepare to receive next byte and acknowledge
		TWCR |= (1<<TWIE) | (1<<TWINT) | (1<<TWEA) | (1<<TWEN); 
	} else if ( (TWSR & 0xF8) == TW_SR_DATA_ACK ){
		// data has been received in slave receiver mode
		uint8_t data = TWDR;
		TWCR |= (1<<TWIE) | (1<<TWINT) | (0<<TWEA) | (1<<TWEN);	
		cmd(data);
	} else {
		// if none of the above apply prepare TWI to be addressed again
		TWCR |= (1<<TWIE) | (1<<TWEA) | (1<<TWEN);
	}
}

ISR(TIMER2_COMP_vect) {
	led_i++;

	if (led_i == 0 && led_r != 0) {
		cbi(PORTD, PD4);
	} 
	if (led_i == 0 && led_g != 0) {
		cbi(PORTD, PD5);
	} 
	if (led_i == 0 && led_b != 0) {
		cbi(PORTD, PD7);
	} 

	if (led_i == led_r) {
		sbi(PORTD, PD4);
	}
	if (led_i == led_g) {
		sbi(PORTD, PD5);
	}
	if (led_i == led_b) {
		sbi(PORTD, PD7);
	}

}

ISR(TIMER1_COMPA_vect) {
	if (floppy_pos == FLOPPY_MAX_POS) {
		sbi(PORTB, PB2); // Direction: Down
	}
	if (floppy_pos == 0) {
		cbi(PORTB, PB2); // Direction: Up
	}

	PORTB & (1 << PB2) ? floppy_pos-- : floppy_pos++;
	PORTB = PINB ^ (1 << PB3);
}

void head_move_start() {
	set_led32(0x00FF0000);
	uart_puts("Moving head to home position...");

	sbi(PORTB, PB2); // Direction: Down
	uint8_t i = FLOPPY_MAX_POS + 10;
	while (i > 0) {
		i--;		
		PORTB = PINB ^ (1 << PB3);
		_delay_ms(5);
	}
	cbi(PORTB, PB2); // Direction: up

	uart_puts("completed.\r\n");
	set_led32(0x0000FF00);
	_delay_ms(200);
	set_led32(0x00000000);
}

int main (void) {
	// Prepare LED port
	sbi(DDRD, PD4); // R
	sbi(PORTD, PD4);
	sbi(DDRD, PD5); // G
	sbi(PORTD, PD5);
	sbi(DDRD, PD7); // B
	sbi(PORTD, PD7);

	// Prepare I2C ADDR port
	PORTA = 0xFF;
	DDRA = 0x00;

	// Prepare FLOPPY port
	sbi(DDRB, PB1); // Motor
	cbi(PORTB, PB1); // Enable motor
	sbi(DDRB, PB2); // Direction
	sbi(DDRB, PB3); // Tick

	sei();

	// LED Timer
	OCR2 = 0x04;
	TCCR2 |= (1 << WGM21); // CTC
	TCCR2 |= (1 << CS22); // Prescaler 64
	TIMSK |= (1 << OCIE2);

	// Floppy Timer
	OCR1A = note_tick[127];
	TCCR1B |= (1 << WGM12); // CTC
	TCCR1B |= (1 << CS11); // Prescaler 8

	uart_init(UART_BAUD_SELECT_DOUBLE_SPEED(UART_BAUD_RATE, F_CPU)); 
	uart_puts("\r\nRRFDC http://schoar.de/tinkering/rumblerail\r\n");

	uint8_t addr = ~PINA & 0xFE;
	TWAR = addr;
	TWCR = (1<<TWIE) | (1<<TWEA) | (1<<TWINT) | (1<<TWEN);

	set_led32(0x000000FF);
	_delay_ms(400);

	sprintf(out, "I2C address is 0x%02x\r\n", addr);
    	uart_puts(out);

	head_move_start();

	uart_puts("Ready to rock!");

	cmd(0xFD); // Idle

	while(mode != OFF) {
		set_sleep_mode(SLEEP_MODE_IDLE);
		sleep_mode();
	}

	uart_puts("Shutdown...\r\n");

	cli();

	sbi(PORTD, PD4); sbi(PORTD, PD5); sbi(PORTD, PD7); // LEDs off
	sbi(PORTB, PB1); // Disable motor

	set_sleep_mode(SLEEP_MODE_PWR_DOWN);
	sleep_mode();

	return 0;
}

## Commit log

2014-01-03 Initial public release, yeah!
